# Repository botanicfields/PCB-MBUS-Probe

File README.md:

# PCB-MBUS-Probe
a Printed Circuit Board to Probe M-Bus of M5Stack

# M-Busプローブ基板キット
M5StackのM-Bus信号をピンソケットに取り出すプローブ基板のキットです。M-Busモジュールに重ねて取り付けて使用します。
- ブレッドボード用のジャンパーワイヤーを直接挿せます。
- M-Bus信号を観測しながらのM-Busモジュールの調整や試験が、プローブ基板の開口部からできます。
- ボトムに出ていないM-Bus信号を観測できます。

## 委託販売（スイッチサイエンス）
https://www.switch-science.com/catalog/7370/

## 内容物
- プリント基板 ×1
- M-Bus用ピンヘッダ(M5Stack純正品) ×1
- ピンソケット(SMD一般用15ピン2列) ×1

## ご注意
- 組み立てには、はんだ付け（表面実装）が必要です。
- 取り扱い説明書はありません。

## 使用例
RTCモジュールのCLKO信号を、M-Busプローブ基板のGPIO36から取り出して周波数カウンタで観測しながら、RTCモジュールの水晶発振子のトリマを調整しています。

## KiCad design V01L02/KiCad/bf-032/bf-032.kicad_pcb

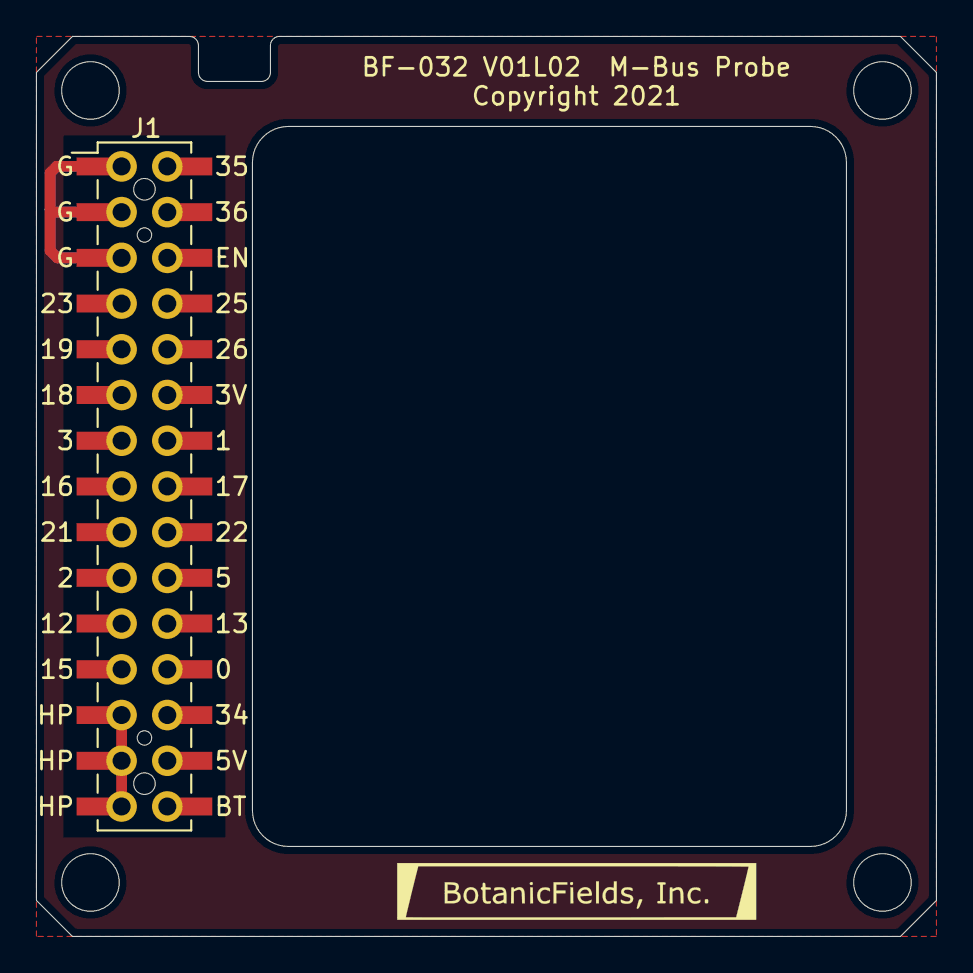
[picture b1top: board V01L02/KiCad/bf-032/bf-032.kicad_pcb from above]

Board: 2 copper layers, 50.0 x 50.0 mm, 5 parts (0 on the bottom side), 2 nets.

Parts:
H1, H2, H3, H4: MountingHole; BF@MountingHole_3.2mm_M3
J1: M-BUS; BF@M5Stack_MBUS

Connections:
GND: J1.2, J1.4, J1.6
VBUS: J1.26, J1.28, J1.30

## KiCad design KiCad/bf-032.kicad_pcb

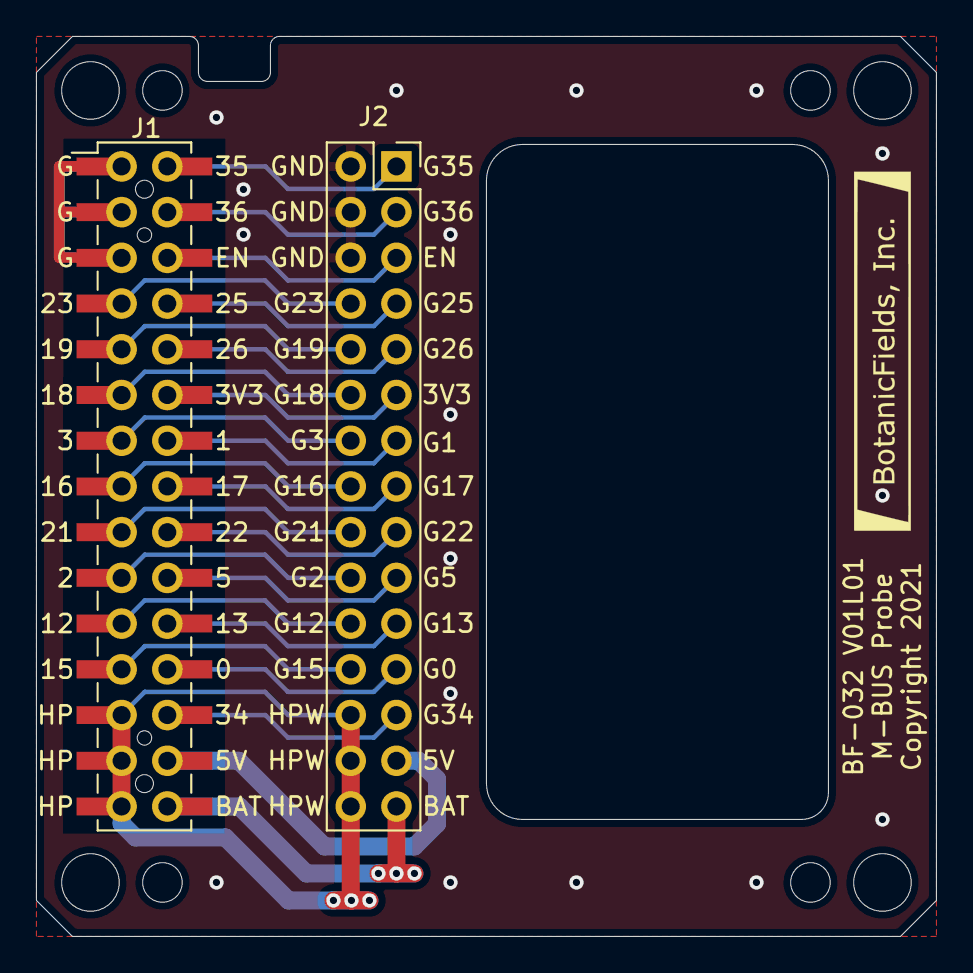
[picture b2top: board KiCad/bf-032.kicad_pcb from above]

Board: 2 copper layers, 50.0 x 50.0 mm, 10 parts (0 on the bottom side), 26 nets.

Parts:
H1, H2, H3, H4: MountingHole; BF@MountingHole_3.2mm_M3
H5, H6, H7, H8: MountingHole; BF@MountingHole_2.2mm_M2
J1: M-BUS; BF@M5Stack_MBUS
J2: PORT; PinSocket_2x15_P2.54mm_Vertical

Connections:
+3V3: J1.11, J2.11
+5V: J1.27, J2.27
+BATT: J1.29, J2.29
/EN: J1.5, J2.5
/GPIO0: J1.23, J2.23
/GPIO1: J1.13, J2.13
/GPIO2: J1.20, J2.20
/GPIO3: J1.14, J2.14
/GPIO5: J1.19, J2.19
/GPIO12: J1.22, J2.22
/GPIO13: J1.21, J2.21
/GPIO15: J1.24, J2.24
/GPIO16: J1.16, J2.16
/GPIO17: J1.15, J2.15
/GPIO18: J1.12, J2.12
/GPIO19: J1.10, J2.10
/GPIO21: J1.18, J2.18
/GPIO22: J1.17, J2.17
/GPIO23: J1.8, J2.8
/GPIO25: J1.7, J2.7
/GPIO26: J1.9, J2.9
/GPIO34: J1.25, J2.25
/GPIO35: J1.1, J2.1
/GPIO36: J1.3, J2.3
GND: J1.2, J1.4, J1.6, J2.2, J2.4, J2.6
VBUS: J1.26, J1.28, J1.30, J2.26, J2.28, J2.30

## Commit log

2021-06-12 V01L01
    New
2021-07-18 V01L02

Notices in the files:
KiCad/bf-032.kicad_pcb:
Copyright 2021 BotanicFields, Inc.
